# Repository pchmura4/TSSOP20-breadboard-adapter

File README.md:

# TSSOP20-breadboard-adapter
Simple breadboard adapter made for low cost STM32 microcontrollers in mind

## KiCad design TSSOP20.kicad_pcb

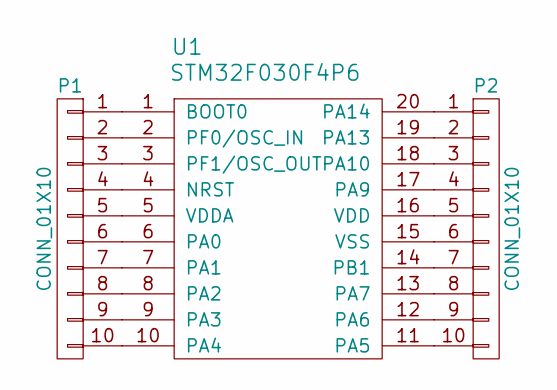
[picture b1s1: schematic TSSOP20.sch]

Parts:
P1, P2: CONN_01X10; Pin_Header_Straight_1x10
U1: STM32F030F4P6; SSOP-20

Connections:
unnamed: P1.1, U1.1 (BOOT0)
unnamed: P1.2, U1.2 (PF0/OSC_IN)
unnamed: P1.3, U1.3 (PF1/OSC_OUT)
unnamed: P1.4, U1.4 (NRST)
unnamed: P1.5, U1.5 (VDDA)
unnamed: P1.6, U1.6 (PA0)
unnamed: P1.7, U1.7 (PA1)
unnamed: P1.8, U1.8 (PA2)
unnamed: P1.9, U1.9 (PA3)
unnamed: P1.10, U1.10 (PA4)
unnamed: P2.1, U1.20 (PA14)
unnamed: P2.2, U1.19 (PA13)
unnamed: P2.3, U1.18 (PA10)
unnamed: P2.4, U1.17 (PA9)
unnamed: P2.5, U1.16 (VDD)
unnamed: P2.6, U1.15 (VSS)
unnamed: P2.7, U1.14 (PB1)
unnamed: P2.8, U1.13 (PA7)
unnamed: P2.9, U1.12 (PA6)
unnamed: P2.10, U1.11 (PA5)

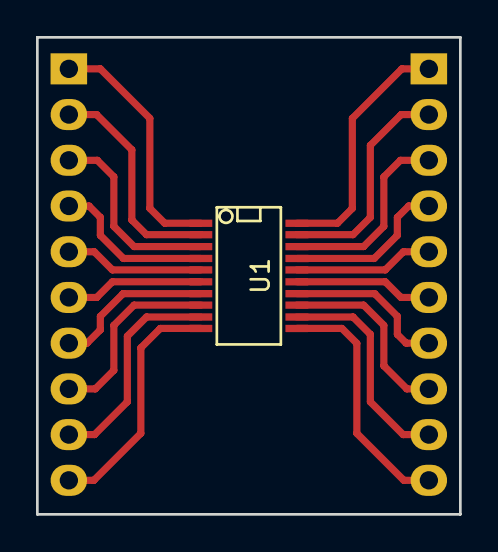
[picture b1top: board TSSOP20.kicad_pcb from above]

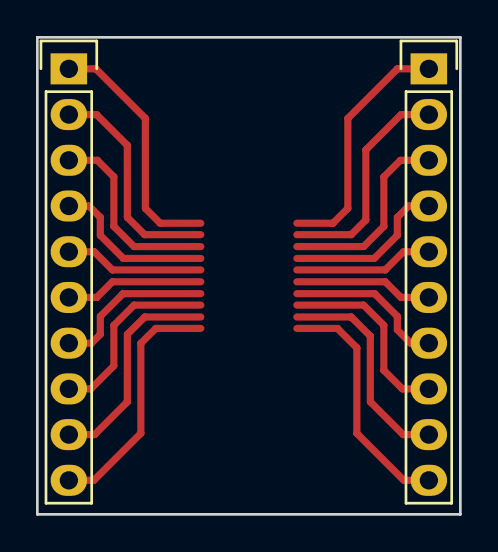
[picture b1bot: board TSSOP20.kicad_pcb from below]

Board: 2 copper layers, 23.5 x 26.5 mm, 3 parts (2 on the bottom side), 20 nets.
